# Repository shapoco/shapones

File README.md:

# [WIP] ShapoNES

an NES emulator for my programming study.

> [!CAUTION]
> It is still in the trial-and-error phase and will be subject to frequent changes.

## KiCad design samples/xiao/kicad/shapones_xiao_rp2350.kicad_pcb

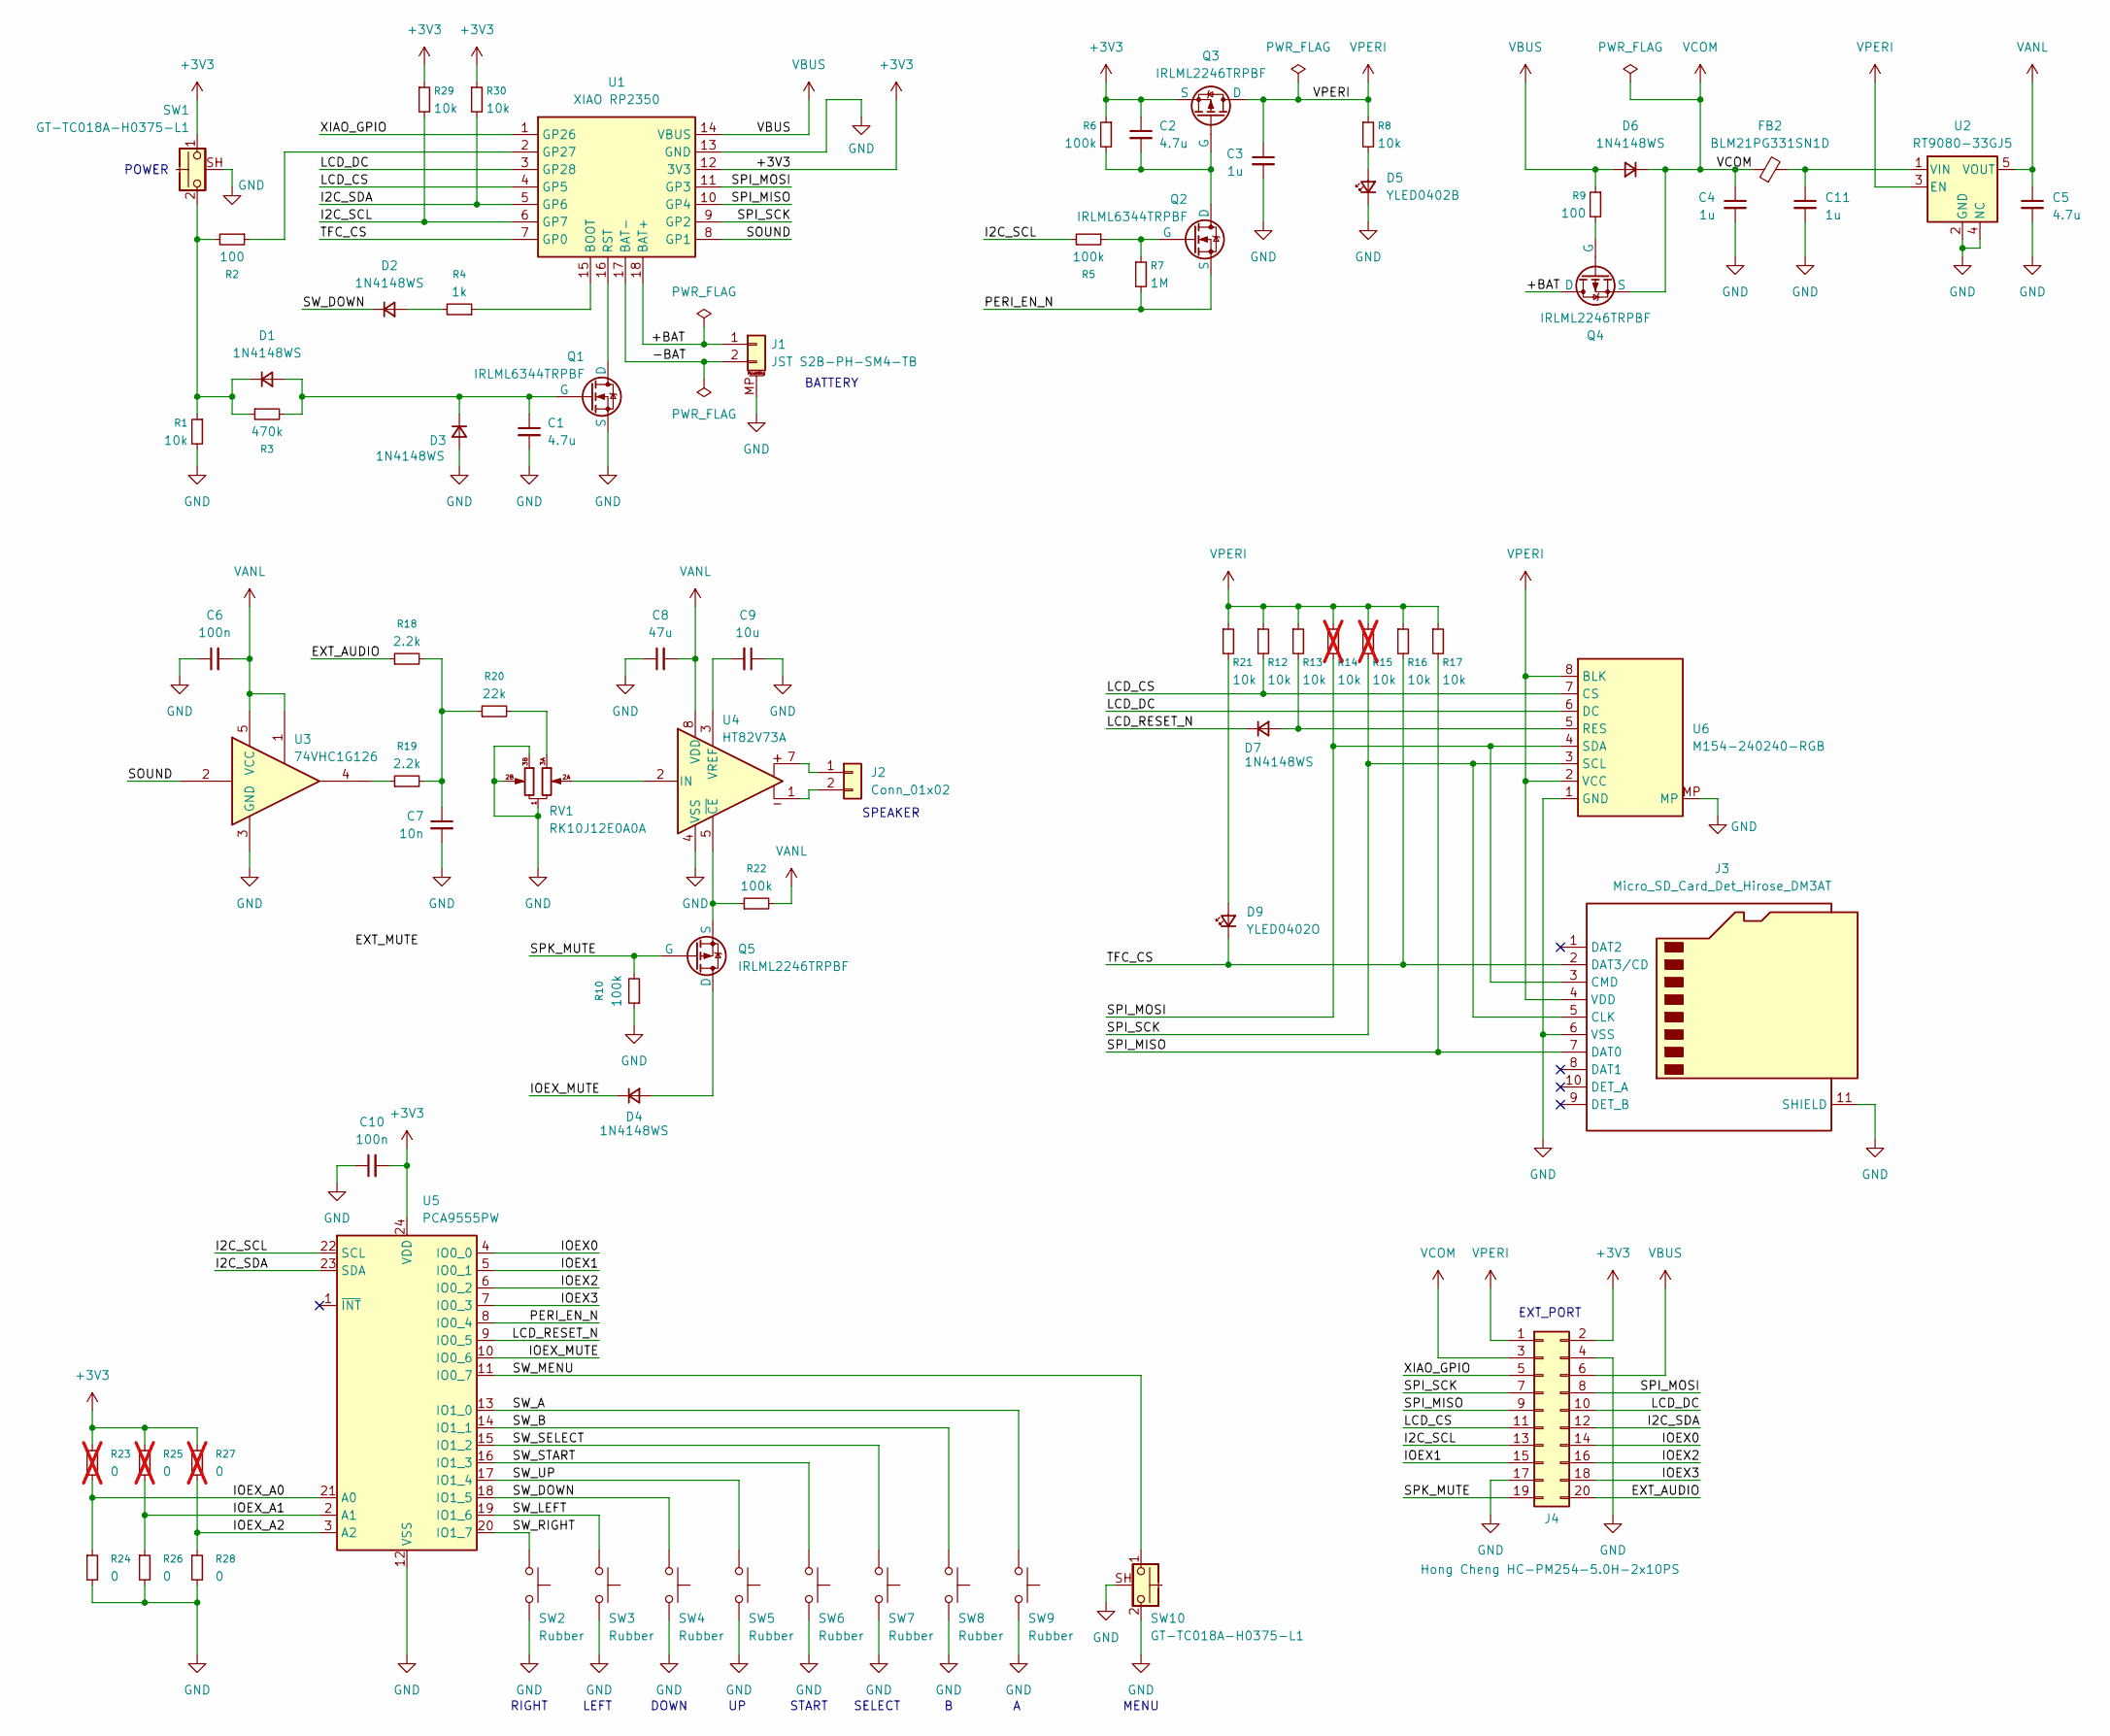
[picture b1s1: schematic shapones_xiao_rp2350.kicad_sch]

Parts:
C1, C2, C5: 4.7u; C_0603_1608Metric; LCSC C1705
C3, C4, C11: 1u; C_0402_1005Metric; LCSC C14445
C6, C10: 100n; C_0402_1005Metric; LCSC C1525
C7: 10n; C_0402_1005Metric; LCSC C15195
C8: 47u; C_0603_1608Metric; LCSC C140782
C9: 10u; C_0603_1608Metric; LCSC C1691
D1, D2, D3, D4, D6, D7: 1N4148WS; D_SOD-323; LCSC C60580
D5: YLED0402B; LED_0402_1005Metric; LCSC C30584803
D9: YLED0402O; LED_0402_1005Metric; LCSC C28310436
FB2: BLM21PG331SN1D; L_0805_2012Metric; LCSC C74764
J1: JST S2B-PH-SM4-TB; JST_PH_S2B-PH-SM4-TB_1x02-1MP_P2.00mm_Horizontal; LCSC C295747
J2: Conn_01x02; SolderWirePad_1x02_SMD_150x50mil
J3: Micro_SD_Card_Det_Hirose_DM3AT; microSD_HC_Hirose_DM3AT-SF-PEJM5; LCSC C114218
J4: Hong Cheng HC-PM254-5.0H-2x10PS; PinSocket_2x10_P2.54mm_Vertical_SMD; LCSC C42163138
Q1, Q2: IRLML6344TRPBF; SOT-23; LCSC C53550
Q3, Q4, Q5: IRLML2246TRPBF; SOT-23; LCSC C127272
R1, R8, R12, R13, R16, R17, R21, R29, R30: 10k; R_0402_1005Metric; LCSC C60490
R2, R9: 100; R_0402_1005Metric; LCSC C1545
R3: 470k; R_0402_1005Metric; LCSC C137976
R4: 1k; R_0402_1005Metric; LCSC C106235
R5: 100k; R_0402_1005Metric; LCSC C60490
R6, R10, R22: 100k; R_0402_1005Metric; LCSC C60491
R7: 1M; R_0402_1005Metric; LCSC C60491
R14, R15: 10k; R_0402_1005Metric; LCSC C60490; not fitted
R18, R19: 2.2k; R_0402_1005Metric; LCSC C114762
R20: 22k; R_0402_1005Metric; LCSC C82868
R23, R25, R27: 0; R_0402_1005Metric; LCSC C106231; not fitted
R24, R26, R28: 0; R_0402_1005Metric; LCSC C106231
RV1: RK10J12E0A0A; RK10J1xE; LCSC C351176
SW1, SW10: GT-TC018A-H0375-L1; LCSC C963235
SW2, SW3, SW4, SW5, SW6, SW7, SW8, SW9: Rubber; Rubber_Contact
U1: XIAO RP2350
U2: RT9080-33GJ5; TSOT-23-5; LCSC C841192
U3: 74VHC1G126; SOT-23-5; LCSC C53100485
U4: HT82V73A; SOIC-8_with_Thermal_Hole
U5: PCA9555PW; TSSOP-24_4.4x7.8mm_P0.65mm; LCSC C128392
U6: M154-240240-RGB

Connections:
+3V3: C2.1, C10.2, J4.2, Q3.3 (S), R6.1, R23.1, R25.1, R27.1, R29.1, R30.1, SW1.1, U1.12 (3V3), U5.24 (VDD)
/+BAT: J1.1, Q4.1 (D), U1.18 (BAT+)
/-BAT: J1.2, U1.17 (BAT-)
/EXT_AUDIO: J4.20, R18.1
/I2C_SCL: J4.13, R5.2, R29.2, U1.6 (GP7), U5.22 (SCL)
/I2C_SDA: J4.12, R30.2, U1.5 (GP6), U5.23 (SDA)
/IOEX0: J4.14, U5.4 (IO0_0)
/IOEX1: J4.15, U5.5 (IO0_1)
/IOEX2: J4.16, U5.6 (IO0_2)
/IOEX3: J4.18, U5.7 (IO0_3)
/IOEX_A0: R23.2, R24.1, U5.21 (A0)
/IOEX_A1: R25.2, R26.1, U5.2 (A1)
/IOEX_A2: R27.2, R28.1, U5.3 (A2)
/IOEX_MUTE: D4.1 (K), U5.10 (IO0_6)
/LCD_CS: J4.11, R12.2, U1.4 (GP5), U6.7 (CS)
/LCD_DC: J4.10, U1.3 (GP28), U6.6 (DC)
/LCD_RESET_N: D7.1 (K), U5.9 (IO0_5)
/PERI_EN_N: Q2.3 (S), R7.2, U5.8 (IO0_4)
/SOUND: U1.8 (GP1), U3.2
/SPI_MISO: J3.7 (DAT0), J4.9, R17.2, U1.10 (GP4)
/SPI_MOSI: J3.3 (CMD), J4.8, R14.2, U1.11 (GP3), U6.4 (SDA)
/SPI_SCK: J3.5 (CLK), J4.7, R15.2, U1.9 (GP2), U6.3 (SCL)
/SPK_MUTE: J4.19, Q5.2 (G), R10.2
/SW_A: SW9.1, U5.13 (IO1_0)
/SW_B: SW8.1, U5.14 (IO1_1)
/SW_DOWN: D2.1 (K), SW4.1, U5.18 (IO1_5)
/SW_LEFT: SW3.1, U5.19 (IO1_6)
/SW_MENU: SW10.1, U5.11 (IO0_7)
/SW_RIGHT: SW2.1, U5.20 (IO1_7)
/SW_SELECT: SW7.1, U5.15 (IO1_2)
/SW_START: SW6.1, U5.16 (IO1_3)
/SW_UP: SW5.1, U5.17 (IO1_4)
/TFC_CS: D9.1 (K), J3.2 (DAT3/CD), R16.2, U1.7 (GP0)
/XIAO_GPIO: J4.5, U1.1 (GP26)
GND: C1.2, C3.2, C4.2, C5.2, C6.1, C7.2, C8.1, C9.1, C10.1, C11.2, D3.2 (A), D5.1 (K), J1.MP (MountPin), J3.6 (VSS), J3.11 (SHIELD), J4.4, J4.17, Q1.3 (S), R1.2, R10.1, R24.2, R26.2, R28.2, RV1.1, RV1.2B, RV1.3B, SW1.SH (B), SW2.2, SW3.2, SW4.2, SW5.2, SW6.2, SW7.2, SW8.2, SW9.2, SW10.2, SW10.SH (B), U1.13 (GND), U2.2 (GND), U2.4 (NC), U3.3 (GND), U4.4 (VSS), U5.12 (VSS), U6.1 (GND), U6.MP
unnamed: C7.1, R18.2, R19.2, R20.1
unnamed: C1.1, D1.2 (A), D3.1 (K), Q1.2 (G), R3.2
unnamed: D1.1 (K), R1.1, R2.2, R3.1, SW1.2
unnamed: D2.2 (A), R4.2
unnamed: D4.2 (A), Q5.1 (D)
unnamed: D5.2 (A), R8.2
unnamed: D7.2 (A), R13.2, U6.5 (RES)
unnamed: D9.2 (A), R21.2
unnamed: J2.1, U4.7
unnamed: J2.2, U4.1
unnamed: Q1.1 (D), U1.16 (RST)
unnamed: C2.2, Q2.1 (D), Q3.2 (G), R6.2
unnamed: Q2.2 (G), R5.1, R7.1
unnamed: Q4.2 (G), R9.2
unnamed: Q5.3 (S), R22.1, U4.5 (~CE)
unnamed: R19.1, U3.4
unnamed: R20.2, RV1.3A
unnamed: R4.1, U1.15 (BOOT)
unnamed: R2.1, U1.2 (GP27)
unnamed: C11.1, FB2.2, U2.1 (VIN)
unnamed: RV1.2A, U4.2 (IN)
unnamed: C9.2, U4.3 (VREF)
VANL: C5.1, C6.2, C8.2, R22.2, U2.5 (VOUT), U3.1, U3.5 (VCC), U4.8 (VDD)
VBUS: D6.2 (A), J4.6, R9.1, U1.14 (VBUS)
VCOM: C4.1, D6.1 (K), FB2.1, J4.3, Q4.3 (S)
VPERI: C3.1, J3.4 (VDD), J4.1, Q3.1 (D), R8.1, R12.1, R13.1, R14.1, R15.1, R16.1, R17.1, R21.1, U2.3 (EN), U6.2 (VCC), U6.8 (BLK)

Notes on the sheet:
LEFT
BATTERY
DOWN
SELECT
RIGHT
SPEAKER
START
EXT_PORT
POWER
MENU

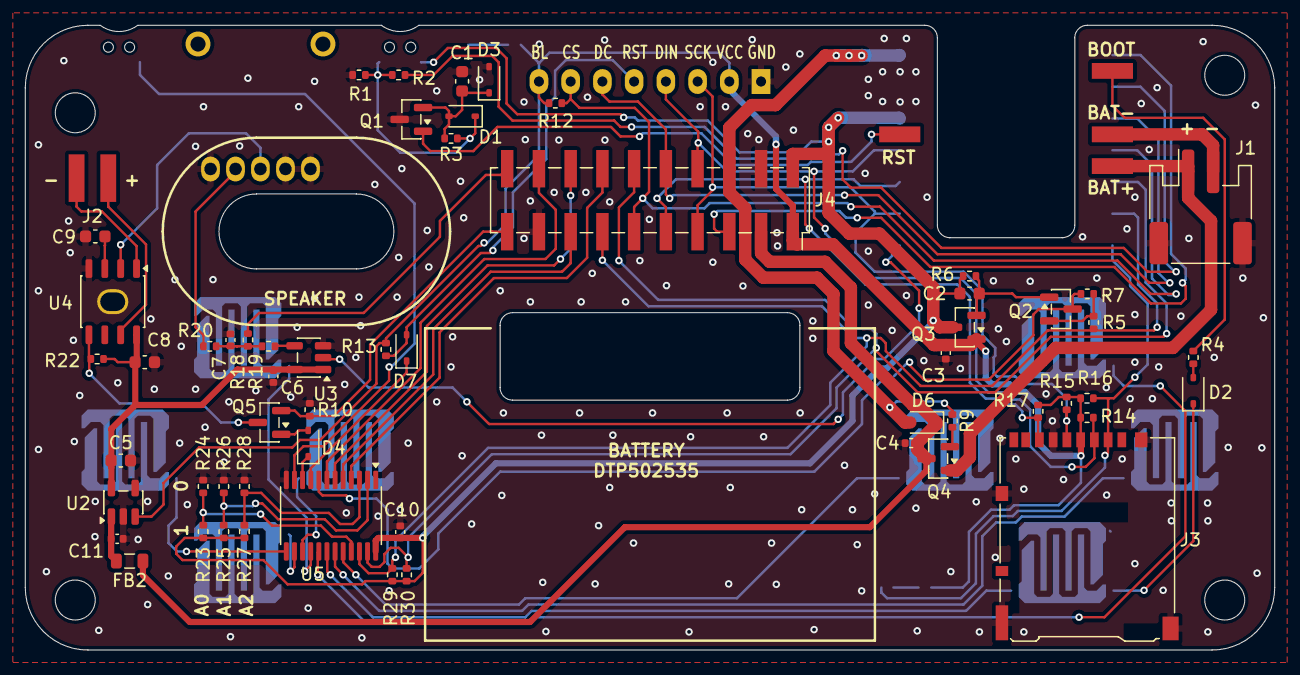
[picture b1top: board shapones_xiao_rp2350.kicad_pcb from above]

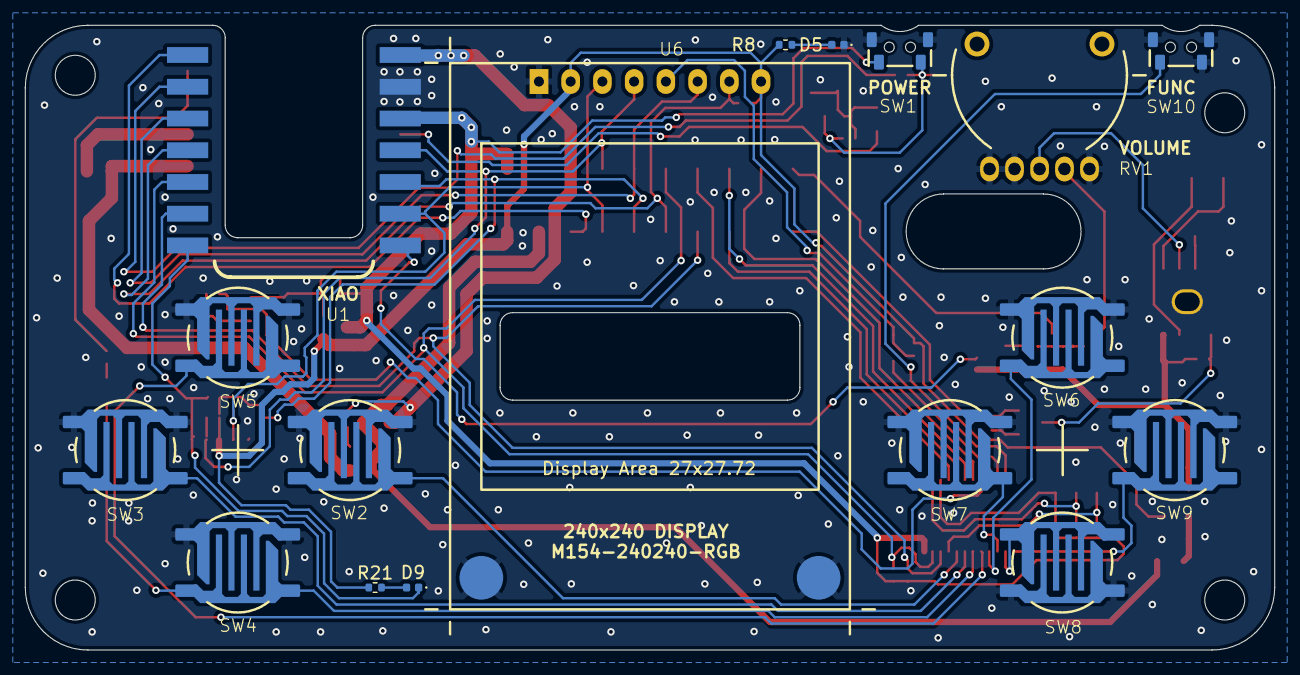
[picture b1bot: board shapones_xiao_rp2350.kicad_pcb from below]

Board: 2 copper layers, 100.0 x 50.0 mm, 75 parts (17 on the bottom side), 61 nets.

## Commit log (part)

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2022-10-31 1st. commmit
2022-10-31 file rename
2022-10-31 add cover image
2022-10-31 update Makefile
2022-10-31 fix PPU bug
2022-10-31 remove PPU startup delay
2022-10-31 optimize CPU
2022-10-31 optimize input latch
2022-10-31 optimize vsync
2022-10-31 PPU optimization
2022-11-01 CPU optimization
2022-11-02 rename basic.hpp to common.hpp
2022-11-02 support WAVESHARE-19804
2022-11-02 change SPI to PIO
2022-11-04 support input
2022-11-05 unsupport WAVESHARE-19579
2022-11-06 preliminary APU support
2022-11-08 refactoring
2022-11-09 add font
2022-11-09 preliminary microSD support
2022-11-09 change cmakelist
2022-11-11 support APU for wxapp
2022-11-11 support Mapper 3
2022-11-12 APU update
2022-11-13 add FPS measurement
2022-11-13 simplify sprite rendering
2022-11-13 cancel previous change
2022-11-13 move RGB444 conversion to core0
2022-11-14 change README
2022-11-14 update image
2026-01-11 MMC3 support
2026-01-12 lock management and configuration updates for APU and PPU
2026-01-12 init: call reset after initialization and adjust load order in wxapp
2026-01-12 docs: add instructions for integrating ShapoNES core and implementing exclusive control functions
2026-01-12 docs: update README with iNES file handling and controller input instructions
2026-01-12 docs: update README to clarify multi-thread operation for CPU services
2026-01-12 docs: update section title for implementing ShapoNES in custom applications
2026-01-13 memory usage reduction
2026-01-13 fix: change SHAPONES_USE_PIO to enable PIO support
2026-01-13 wip: sample app for M5Stack CoreS3
2026-01-14 mapper 1 (MMC1) support
2026-01-15 wip: AtomS3 support
2026-01-19 fix code format
2026-01-19 Refactor vsync handling and add new mappers
    - Updated `wait_vsync` function in `pico_nes_ws19804.cpp` and `disp_wait_vsync` in `main.cpp` to simplify delay logic and return a more meaningful value.
    - Added deinitialization call for NES audio in `nes_app.cpp` during application close.
    - Introduced new mapper classes: `Map000`, `Map001`, `Map003`, and `Map004` to support various NES cartridge types, implementing necessary memory mapping and IRQ handling.
2026-01-19 add schematic for AtomS3
2026-01-23 boot menu added
2026-01-23 MMC2 support, APU noise fixed
2026-01-24 fix for Arduino
2026-01-25 wip: state saving
2026-01-30 fix audio volume for AtomS3
2026-01-30 fix exclusive control
2026-02-01 improve OAM memory access
2026-02-01 improve PPU performance
2026-02-02 namespace changed
2026-02-02 file renamed
2026-02-02 fix font
2026-02-05 experimental: remote
2026-02-05 apply computed goto
2026-02-05 improve CPU performance
2026-02-06 fix for PicoPad
2026-02-06 computed goto --> switch
2026-02-10 wip: support XIAO RP2350
2026-02-12 add schematic
2026-02-14 add deep sleep function
2026-02-16 MCP23017-->PCA9555
2026-02-16 original version of ESP32DMASPI
2026-02-16 ESP32DMASPI: modified to support short transactions.
2026-02-16 wip: XIAO ESP32S3 support
2026-02-16 Add LICENSE
2026-02-16 Add caution note about trial-and-error phase
    Added caution note about the project's current status.
2026-02-16 kicad project moved
2026-02-22 wip: PCB layout
2026-02-22 add tooling strips
2026-02-24 Orders made to JLCPCB
2026-02-27 add codes for XIAO RP2350
2026-02-27 remove old codes
2026-05-08 add sample app for xiamocon
2026-05-08 fix document
